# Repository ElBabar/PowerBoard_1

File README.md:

# PowerBoard_1

KiCad Rackable Power Board for my Robotics club robot, taking part in the Coupe de France de Robotique.

BOM is to come.	

You might need to use my library:
add https://github.com/ElBabar/Libabar.git
to your KiCad paths.

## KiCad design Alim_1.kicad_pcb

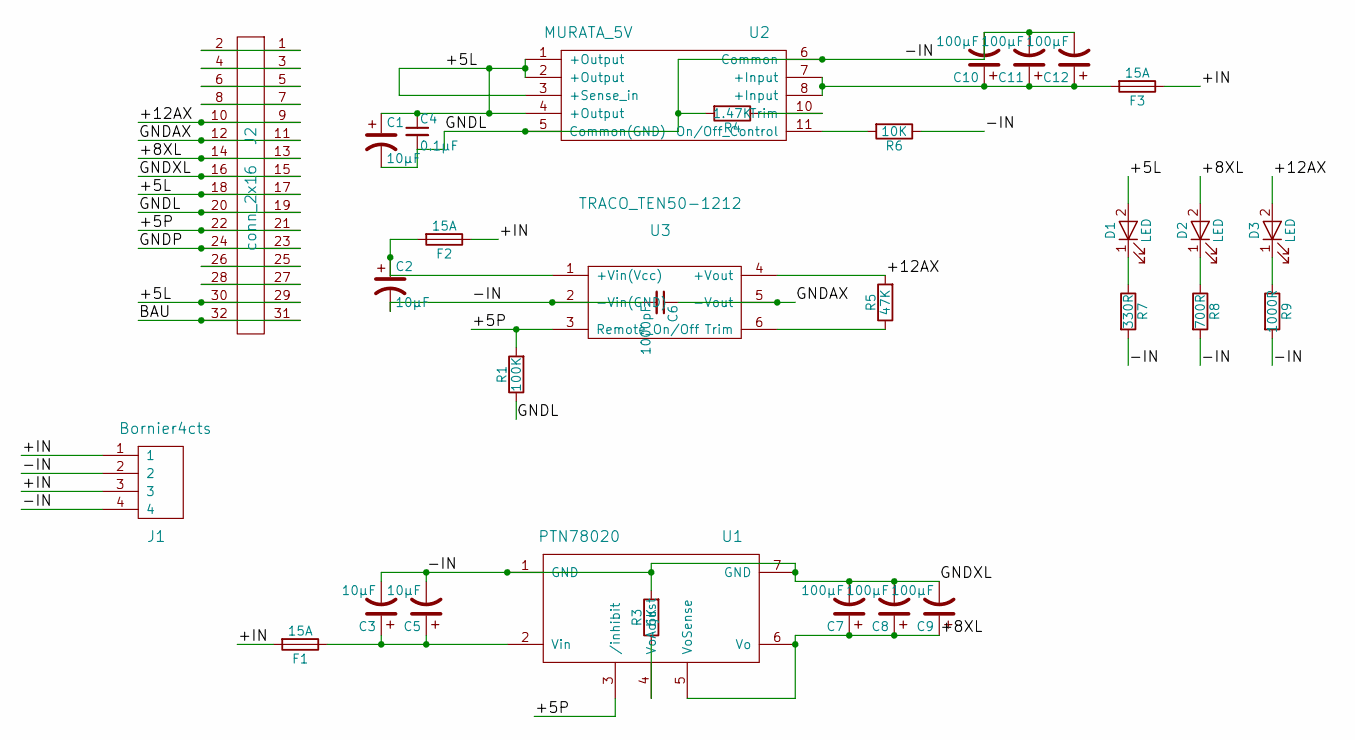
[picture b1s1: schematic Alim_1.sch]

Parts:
C1, C2, C3, C5: 10µF; CP_Radial_D5.0mm_P2.50mm
C4: 0.1µF; C_Disc_D3.8mm_W2.6mm_P2.50mm
C6: 1000pF; C_Disc_D3.8mm_W2.6mm_P2.50mm
C7, C8, C9, C10, C11, C12: 100µF; CP_Radial_D6.3mm_P2.50mm
D1, D2, D3: LED; LED_D3.0mm
F1, F2, F3: 15A; Fuseholder5x20_horiz_open_universal_Type-III
J1: Bornier4cts
J2: conn_2x16
R1: 100K; R_Axial_DIN0207_L6.3mm_D2.5mm_P10.16mm_Horizontal
R3: 6K; R_Axial_DIN0207_L6.3mm_D2.5mm_P10.16mm_Horizontal
R4: 1.47K; R_Axial_DIN0207_L6.3mm_D2.5mm_P10.16mm_Horizontal
R5: 47K; R_Axial_DIN0207_L6.3mm_D2.5mm_P10.16mm_Horizontal
R6: 10K; R_Axial_DIN0207_L6.3mm_D2.5mm_P10.16mm_Horizontal
R7: 330R; R_Axial_DIN0207_L6.3mm_D2.5mm_P10.16mm_Horizontal
R8: 700R; R_Axial_DIN0207_L6.3mm_D2.5mm_P10.16mm_Horizontal
R9: 1000R; R_Axial_DIN0207_L6.3mm_D2.5mm_P10.16mm_Horizontal
U1: PTN78020
U2: MURATA_5V
U3: TRACO_TEN50-1212

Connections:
/+5L: C1.1, C4.1, D1.2 (A), J2.17, J2.18, J2.29, J2.30, U2.1 (+Output), U2.2 (+Output), U2.3 (+Sense_in), U2.4 (+Output)
/+5P: J2.21, J2.22, R1.2, U1.3 (/inhibit), U3.3 (Remote_On/Off)
/+8XL: C7.1, C8.1, C9.1, D2.2 (A), J2.13, J2.14, U1.5 (VoSense), U1.6 (Vo)
/+12AX: D3.2 (A), J2.9, J2.10, R5.2, U3.4 (+Vout)
/+IN: F1.2, F2.1, F3.1, J1.1, J1.3
/-IN: C1.2, C2.2, C3.2, C4.2, C5.2, C6.2, C7.2, C8.2, C9.2, C10.2, C11.2, C12.2, J1.2, J1.4, J2.15, J2.16, J2.19, J2.20, R1.1, R3.2, R4.2, R6.1, R7.2, R8.2, R9.2, U1.1 (GND), U1.7 (GND), U2.5 (Common(GND)), U2.6 (Common), U3.2 (-Vin(GND))
/BAU: J2.31, J2.32
/GNDAX: C6.1, J2.11, J2.12, U3.5 (-Vout)
/GNDP: J2.23, J2.24
unnamed: C2.1, F2.2, U3.1 (+Vin(Vcc))
unnamed: C3.1, C5.1, F1.1, U1.2 (Vin)
unnamed: C10.1, C11.1, C12.1, F3.2, U2.7 (+Input), U2.8 (+Input)
unnamed: D1.1 (K), R7.1
unnamed: D2.1 (K), R8.1
unnamed: D3.1 (K), R9.1
unnamed: J2.1, J2.2
unnamed: J2.3, J2.4
unnamed: J2.5, J2.6
unnamed: J2.7, J2.8
unnamed: J2.25, J2.26
unnamed: J2.27, J2.28
unnamed: R3.1, U1.4 (VoAdjust)
unnamed: R4.1, U2.10 (Trim)
unnamed: R5.1, U3.6 (Trim)
unnamed: R6.2, U2.11 (On/Off_Control)

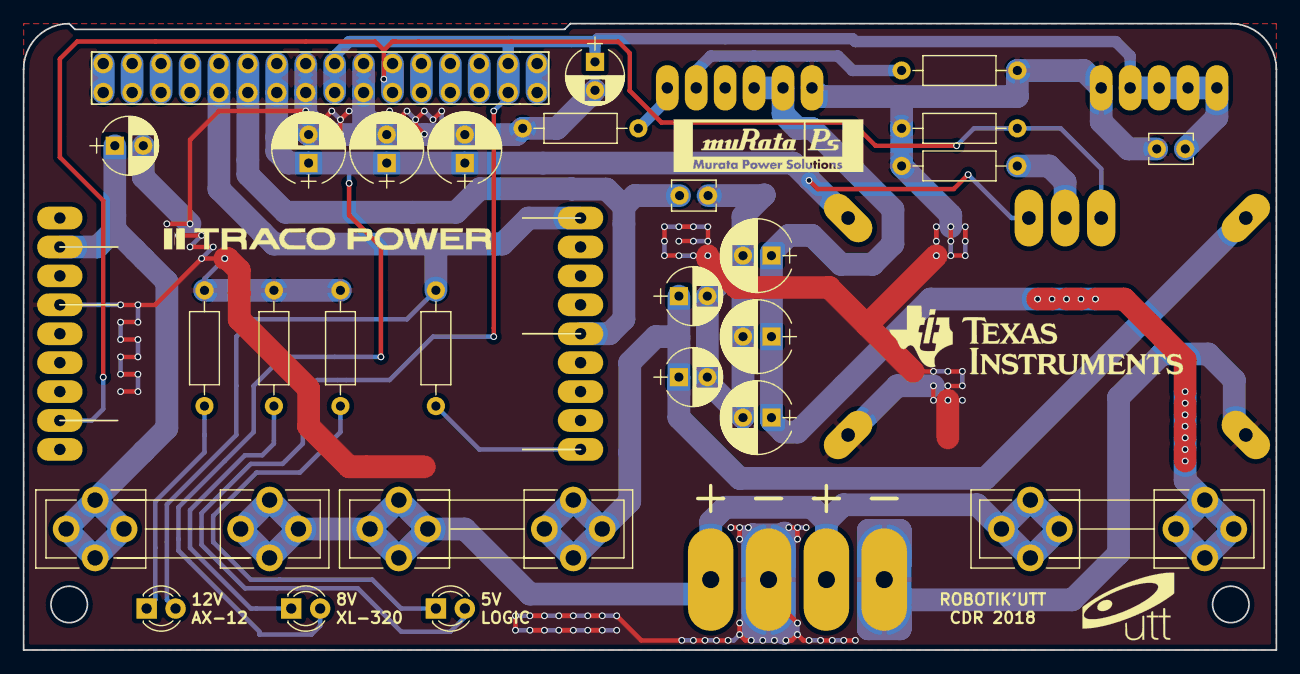
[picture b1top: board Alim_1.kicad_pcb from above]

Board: 2 copper layers, 110.0 x 55.0 mm, 31 parts (0 on the bottom side), 25 nets.

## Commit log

2018-02-07 minor changes
2018-02-07 added generated gerber
